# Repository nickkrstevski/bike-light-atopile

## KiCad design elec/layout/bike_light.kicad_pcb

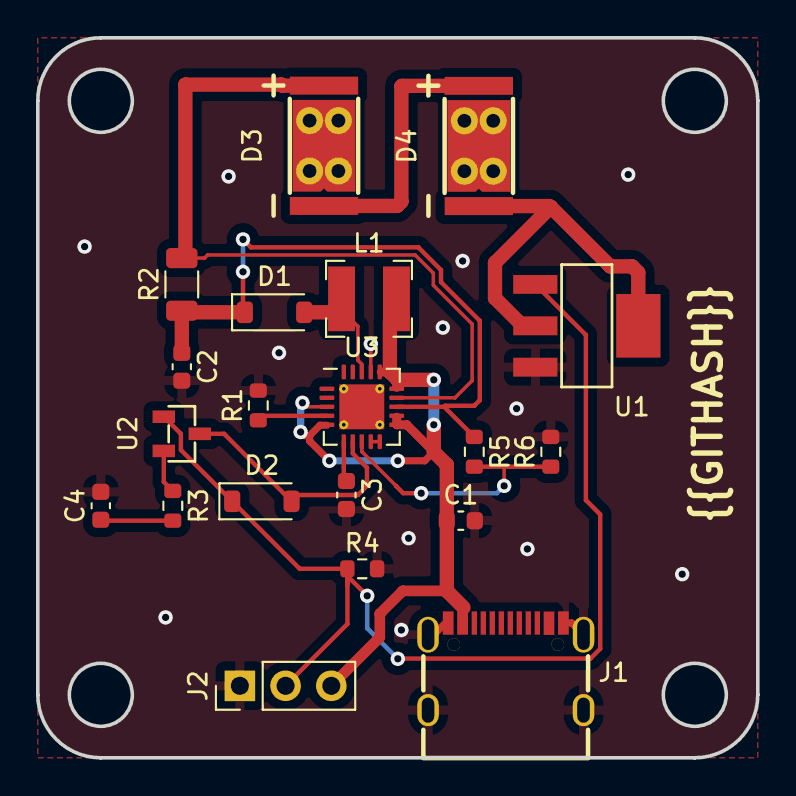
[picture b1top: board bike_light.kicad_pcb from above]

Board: 2 copper layers, 40.0 x 40.0 mm, 20 parts (0 on the bottom side), 19 nets.

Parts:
C1: 3.3uF; C_0603_1608Metric
C2: 10uF; C_0603_1608Metric
C3: 33nF; C_0603_1608Metric
C4: 10nF; C_0603_1608Metric
D1, D2: D_SOD-123
D3, D4: LED-SMD_3P-L7.0-W3.5_XL-C3570P5S10-62C3C2
J1: USB-C-SMD_KH-TYPE-C-16P
J2: PinHeader_1x03_P2.54mm_Vertical
L1: 2.2uH; L_Bourns-SRN4018
R1: 6.81k; R_0603_1608Metric
R2: 1R; R_1206_3216Metric
R3: 2.4k; R_0603_1608Metric
R4: 100k; R_0603_1608Metric
R5: 1M; R_0603_1608Metric
R6: 60.4k; R_0603_1608Metric
U1: SOT-223_L6.5-W3.5-P2.30-LS7.0-BR
U2: SOT-23-3_L2.9-W1.3-P1.90-LS2.4-BR
U3: QFN-20-1EP_4x4mm_P0.5mm_EP2.5x2.5mm_ThermalVias

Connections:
1: C1.1, J1.A4, J1.A9, J1.B4, J1.B9, J2.3, L1.1, U3.3, U3.5, U3.11, U3.12, U3.15, U3.16
2: C1.2, C2.2, C3.2, C4.2, J1.1, J1.2, J1.3, J1.4, J1.A1, J1.A12, J1.B1, J1.B12, J2.1, R1.2, R4.2, R6.2, U1.3, U3.17, U3.21
4: D3.1, D4.3
5: D3.3, R2.2, U3.14
8: D4.1, U1.2, U1.4
11: C2.1, D1.1, R2.1, R5.1, U3.13
12: D2.1, J2.2, R4.1, U1.1, U2.1
15: R1.1, U3.4
16: C3.1, U3.6
17: D2.2, U2.3, U3.7
18: R5.2, R6.1, U3.8
19: U3.9, U3.10
20: D1.2, L1.2, U3.18
32: R3.1, U2.2
34: C4.1, R3.2
38: J1.A6, J1.B6
39: J1.A7, J1.B7
40: J1.A5, J1.B5
41: J1.A8, J1.B8

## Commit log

2023-06-06 add data for new targets
2023-06-10 update for visualizer
2023-06-20 change diode name to match std lib
2023-06-20 create new local class for diode
2023-06-27 change vdiv to increase voltage output
2023-06-27 add 3 pin header
2023-06-27 change pin header file name
2023-06-27 switch to 3 pin header
2023-06-27 add heat sink to LED
2023-06-27 update the layout according to schematic
2023-06-27 update the jlc part numbers
2023-06-27 sink the LEDs to gnd. Needs testing
2023-06-27 update the footprint and layout
2023-06-28 remove heat sink connection
2023-06-28 update footprint with thermal pad
2023-06-28 layout improvements
2023-06-28 Build pos file and BoM in CI
2023-06-28 fill jlc part numbers for new components
2023-06-28 correct 1R resistor JLCPCB part
2023-06-28 switch shunt resistor
2023-06-28 fix jlc pcb bom
2023-06-28 use std resistor
2023-06-28 add check stage to CI
2023-06-28 build all ato targets
2023-06-29 improve layout and add larger inductor
2023-06-29 fix typo
2023-06-30 remove all thermal reliefs from driver chip
2023-07-09 remove antiquated data
2023-07-13 ato pathv2 update - breaking change
2023-07-14 update bike light for vis v2
2023-07-14 Tidy up inverted commas in YAMLs
2023-07-14 cleanup the vis files
2023-07-14 remove v1 vis aspects
2023-07-15 layout sch
2023-07-19 remove all p prefix from pins
